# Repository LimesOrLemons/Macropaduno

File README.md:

# Macropaduno

An ESP32-S3 handheld controller with a custom PCB and 3D-printed enclosure for numerous programmable functions.

## Overview

Welcome to **Macropaduno**, a custom-designed handheld controller powered by an ESP32-S3. This is the second iteration of the design, significantly expanded to pack maximum functionality into a compact layout for advanced programming and testing.

## Features & Hardware Specs

* **Microcontroller:** ESP32-S3
* **Connectivity:** Bluetooth & Wi-Fi
* **Power Management:** Integrated battery management, internal power system, and a voltage booster (3.3V to 5V)
* **Audio:** Onboard speaker driven by an audio amplifier
* **Visuals:** OLED screen, camera module (OV2640), and addressable RGB LED
* **Input Controls:**
* 9x Mechanical key switches
* 2x Pressable joysticks
* 1x Pressable rotary encoder switch

* **Expansion:** Dedicated servo/header port for external peripherals and motors

## Project Journey & Lessons Learned

This design represents about a month of intensive work on the digital and schematic design side. Moving from a much smaller initial prototype, this version integrates all peripheral components onto a single custom PCB paired with a 3D-printed enclosure.

While the form factor turned out a bit bulkier than originally planned, it serves as an exceptional foundation for future iterations. Key engineering takeaways from this project include:

* Introduction to KiCad schematic and PCB layout & practices
* C++ firmware development for the ESP32-S3 and electronic components
* Planning for acoustic chambers, battery integration, and mechanical clearance in 3D CAD (modeled in Onshape, with future plans to explore SolidWorks for professional CAD workflows).
* Identifying areas for future optimization, such as transitioning to 4-layer boards and component stacking for tighter spatial efficiency.

## Version 1 Prototype
Here is what the v1 version of the macropad looked like:

## Version 2 Prototype
Here is what the v2 version of the macropad looked like:

## Acknowledgements & Credits

Special thanks to the open-source community and creators who shared CAD models and reference files used during the design process:

* [603040 600mAh LiPo Battery Cell on GrabCAD](https://grabcad.com/library/603040-600mah-lipo-battery-cell-1)
* [Cherry MX Switches on GrabCAD](https://grabcad.com/library/cherry-mx-switches-mx-1)
* [OV2640 Camera Model on GrabCAD](https://grabcad.com/library/ov2640-for-esp32-cam-1)
* [JST PH 2.0mm Connector Pack on GrabCAD](https://grabcad.com/library/jst-ph-2-0mm-connector-pack-through-hole-smt-ds1066-1)
* [Rotary Encoder on GrabCAD](https://grabcad.com/library/rotary-encoder-17)
* [0.91" OLED 128x32 Display on GrabCAD](https://grabcad.com/library/oled-0-91-128x32-1)
* [CherryMX GitHub Library by hineybush](https://github.com/hineybush/CherryMX/tree/master)

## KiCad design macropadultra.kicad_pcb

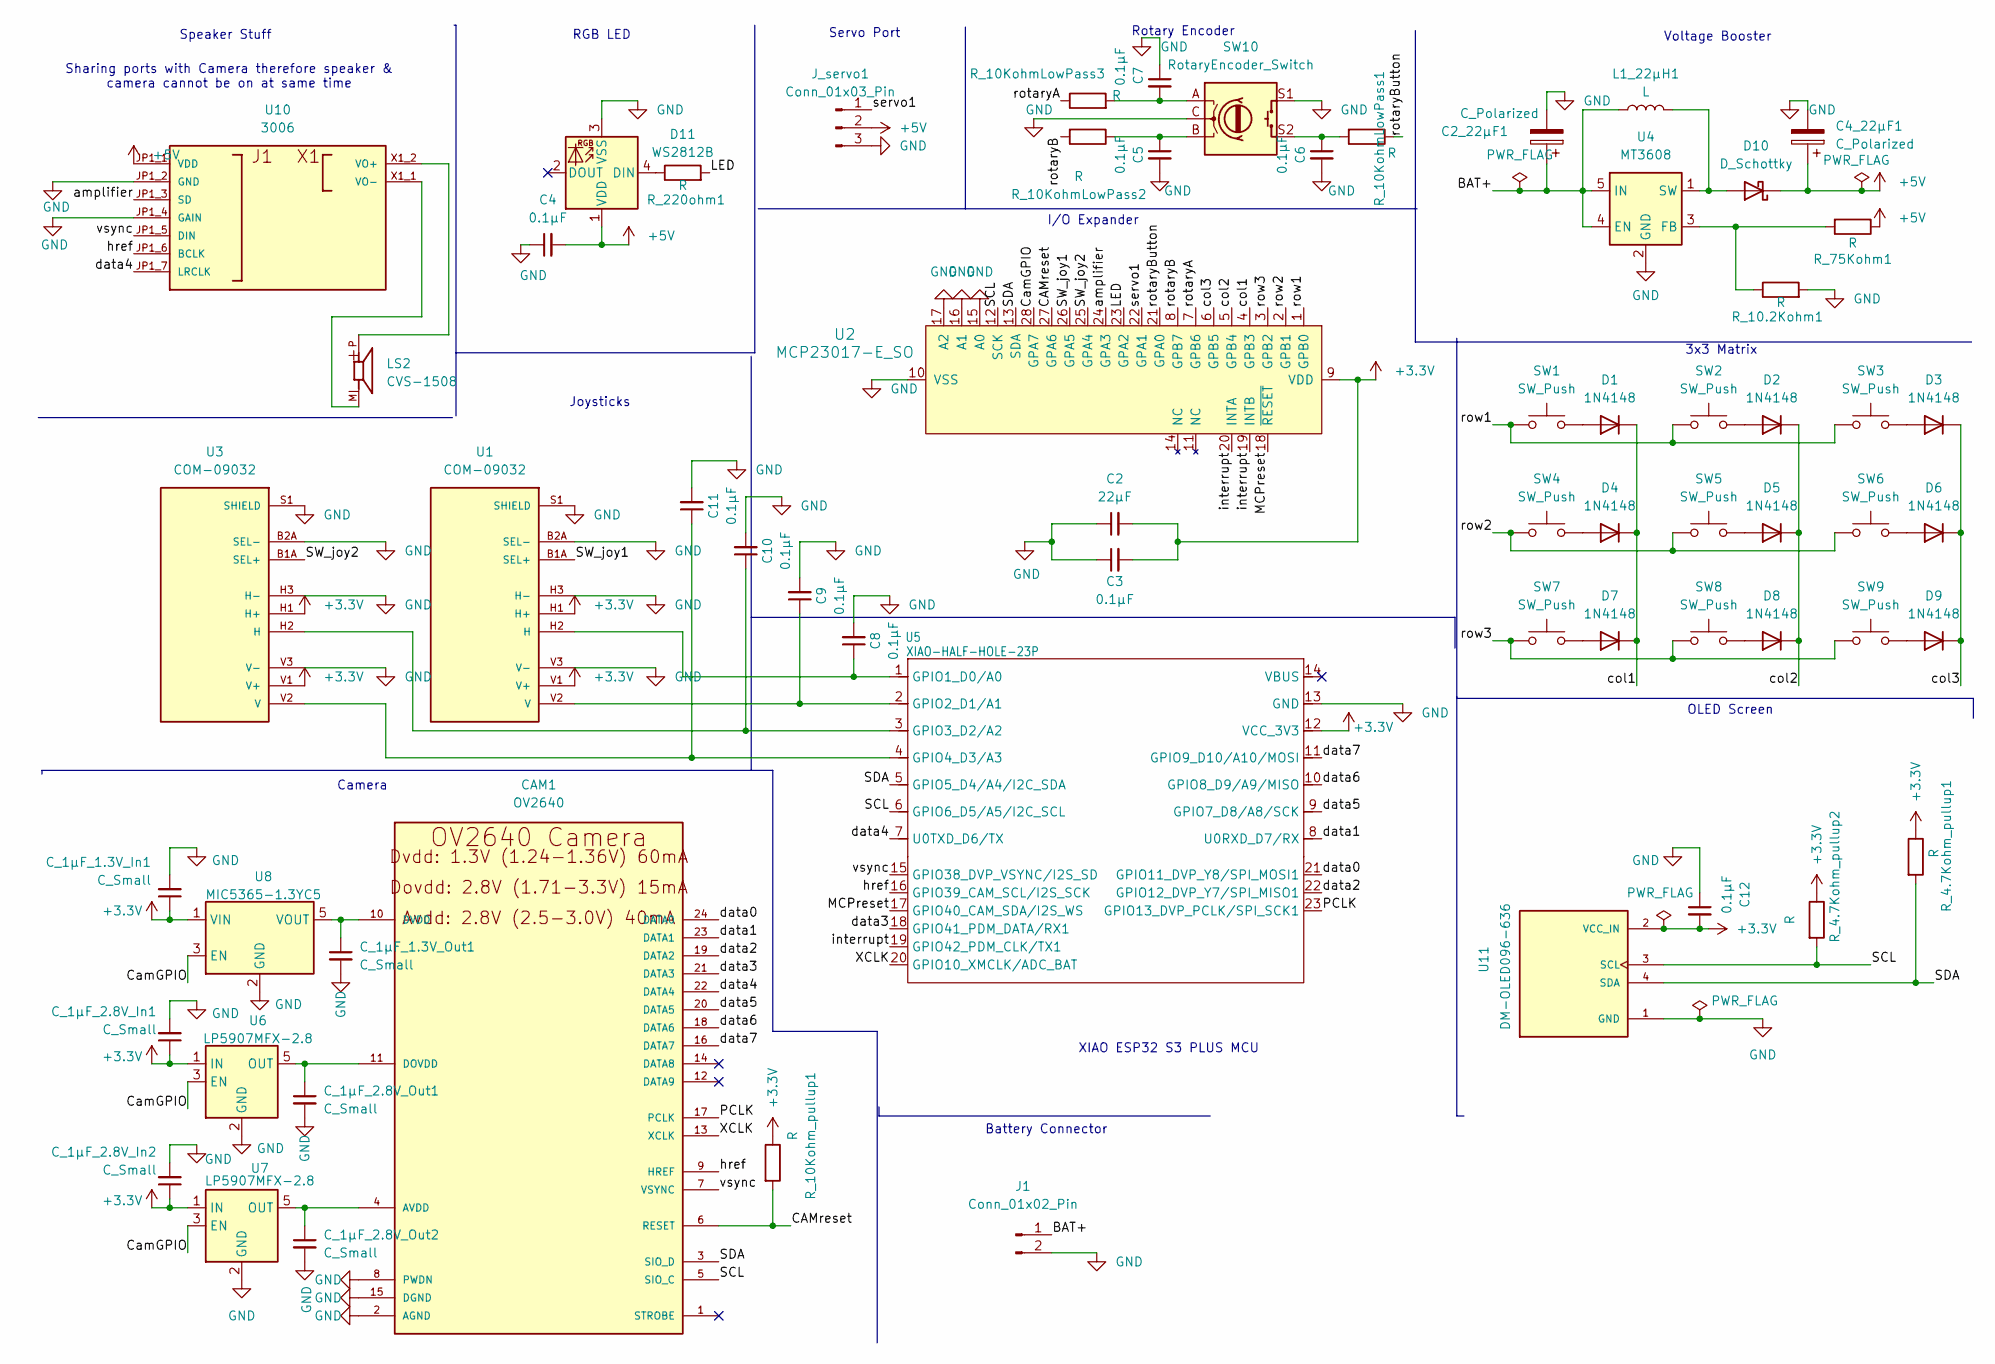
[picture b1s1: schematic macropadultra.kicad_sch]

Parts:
C2: 22µF; C_Disc_D5.0mm_W2.5mm_P5.00mm
C2_22µF1, C4_22µF1: C_Polarized; CP_Radial_D5.0mm_P2.00mm
C3, C4, C5, C6, C7, C8, C9, C10, C11, C12: 0.1µF; C_Disc_D5.0mm_W2.5mm_P5.00mm
CAM1: OV2640
C_1µF_1.3V_In1, C_1µF_1.3V_Out1, C_1µF_2.8V_In1, C_1µF_2.8V_In2, C_1µF_2.8V_Out1, C_1µF_2.8V_Out2: C_Small; C_Disc_D5.0mm_W2.5mm_P5.00mm
D1, D2, D3, D4, D5, D6, D7, D8, D9: 1N4148; D_DO-35_SOD27_P7.62mm_Horizontal
D10: D_Schottky; D_DO-41_SOD81_P10.16mm_Horizontal
D11: WS2812B; LED_WS2812B_PLCC4_5.0x5.0mm_P3.2mm
J1: Conn_01x02_Pin; JST_PH_S2B-PH-SM4-TB_1x02-1MP_P2.00mm_Horizontal
J_servo1: Conn_01x03_Pin; PinHeader_1x03_P2.54mm_Horizontal
L1_22µH1: L; L_Radial_D10.0mm_P5.00mm_Fastron_07M
LS2: CVS-1508; SPKR_CVS-1508
R_4.7Kohm_pullup1, R_4.7Kohm_pullup2, R_10.2Kohm1, R_10KohmLowPass1, R_10KohmLowPass2, R_10KohmLowPass3, R_10Kohm_pullup1, R_75Kohm1, R_220ohm1: R; R_Axial_DIN0207_L6.3mm_D2.5mm_P10.16mm_Horizontal
SW1, SW2, SW3, SW4, SW5, SW6, SW7, SW8, SW9: SW_Push; SW_Cherry_MX_1.00u_PCB
SW10: RotaryEncoder_Switch; RotaryEncoder_Alps_EC11E-Switch_Vertical_H20mm
U1, U3: COM-09032; XDCR_COM-09032; PARTREV N/A
U2: MCP23017-E_SO; SOIC-28_W7.5mm; MPN MCP23017-E/SO; Digi-Key_PN MCP23017-E/SO-ND
U4: MT3608; SOT-23-6
U5: XIAO-HALF-HOLE-23P; XIAO-ESP32-S3-Plus-SMD
U6, U7: LP5907MFX-2.8; SOT-23-5
U8: MIC5365-1.3YC5; SOT-353_SC-70-5
U10: 3006; MODULE_3006; PARTREV A
U11: DM-OLED096-636; MODULE_DM-OLED096-636; PARTREV 2018-09-10

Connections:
+3.3V: C2.2, C3.2, C12.2, C_1µF_1.3V_In1.1, C_1µF_2.8V_In1.1, C_1µF_2.8V_In2.1, R_4.7Kohm_pullup1.1, R_4.7Kohm_pullup2.1, R_10Kohm_pullup1.1, U1.H1 (H+), U1.V1 (V+), U2.9 (VDD), U3.H1 (H+), U3.V1 (V+), U5.12 (VCC_3V3), U6.1 (IN), U7.1 (IN), U8.1 (VIN), U11.2 (VCC_IN)
+5V: C4.2, C4_22µF1.1, D10.1 (K), D11.1 (VDD), J_servo1.2, R_75Kohm1.1, U10.JP1_1 (VDD)
/BAT+: C2_22µF1.1, J1.1, L1_22µH1.1, U4.4 (EN), U4.5 (IN), U5.32
/CAMreset: CAM1.6 (RESET), R_10Kohm_pullup1.2, U2.27 (GPA6)
/CamGPIO: U2.28 (GPA7), U6.3 (EN), U7.3 (EN), U8.3 (EN)
/LED: R_220ohm1.2, U2.23 (GPA2)
/MCPreset: U2.18 (~RESET), U5.17 (GPIO40_CAM_SDA/I2S_WS)
/PCLK: CAM1.17 (PCLK), U5.23 (GPIO13_DVP_PCLK/SPI_SCK1)
/SCL: CAM1.5 (SIO_C), R_4.7Kohm_pullup2.2, U2.12 (SCK), U5.6 (GPIO6_D5/A5/I2C_SCL), U11.3 (SCL)
/SDA: CAM1.3 (SIO_D), R_4.7Kohm_pullup1.2, U2.13 (SDA), U5.5 (GPIO5_D4/A4/I2C_SDA), U11.4 (SDA)
/SW_joy1: U1.B1A (SEL+), U2.26 (GPA5)
/SW_joy2: U2.25 (GPA4), U3.B1A (SEL+)
/XCLK: CAM1.13 (XCLK), U5.20 (GPIO10_XMCLK/ADC_BAT)
/amplifier: U2.24 (GPA3), U10.JP1_3 (SD)
/col1: D1.1 (K), D4.1 (K), D7.1 (K), U2.4 (GPB3)
/col2: D2.1 (K), D5.1 (K), D8.1 (K), U2.5 (GPB4)
/col3: D3.1 (K), D6.1 (K), D9.1 (K), U2.6 (GPB5)
/data0: CAM1.24 (DATA0), U5.21 (GPIO11_DVP_Y8/SPI_MOSI1)
/data1: CAM1.23 (DATA1), U5.8 (U0RXD_D7/RX)
/data2: CAM1.19 (DATA2), U5.22 (GPIO12_DVP_Y7/SPI_MISO1)
/data3: CAM1.21 (DATA3), U5.18 (GPIO41_PDM_DATA/RX1)
/data4: CAM1.22 (DATA4), U5.7 (U0TXD_D6/TX), U10.JP1_7 (LRCLK)
/data5: CAM1.20 (DATA5), U5.9 (GPIO7_D8/A8/SCK)
/data6: CAM1.18 (DATA6), U5.10 (GPIO8_D9/A9/MISO)
/data7: CAM1.16 (DATA7), U5.11 (GPIO9_D10/A10/MOSI)
/href: CAM1.9 (HREF), U5.16 (GPIO39_CAM_SCL/I2S_SCK), U10.JP1_6 (BCLK)
/interrupt: U2.19 (INTB), U2.20 (INTA), U5.19 (GPIO42_PDM_CLK/TX1)
/rotaryA: R_10KohmLowPass3.1, U2.7 (GPB6)
/rotaryB: R_10KohmLowPass2.2, U2.8 (GPB7)
/rotaryButton: R_10KohmLowPass1.1, U2.21 (GPA0)
/row1: SW1.1, SW2.1, SW3.1, U2.1 (GPB0)
/row2: SW4.1, SW5.1, SW6.1, U2.2 (GPB1)
/row3: SW7.1, SW8.1, SW9.1, U2.3 (GPB2)
/servo1: J_servo1.1, U2.22 (GPA1)
/vsync: CAM1.7 (VSYNC), U5.15 (GPIO38_DVP_VSYNC/I2S_SD), U10.JP1_5 (DIN)
GND: C2.1, C2_22µF1.2, C3.1, C4.1, C4_22µF1.2, C5.2, C6.2, C7.1, C8.2, C9.2, C10.2, C11.2, C12.1, CAM1.2 (AGND), CAM1.8 (PWDN), CAM1.15 (DGND), CAM1.MT1 (DGND), CAM1.MT2 (DGND), C_1µF_1.3V_In1.2, C_1µF_1.3V_Out1.2, C_1µF_2.8V_In1.2, C_1µF_2.8V_In2.2, C_1µF_2.8V_Out1.2, C_1µF_2.8V_Out2.2, D11.3 (VSS), J1.2, J_servo1.3, R_10.2Kohm1.2, SW10.C, SW10.S1, U1.B2A (SEL-), U1.H3 (H-), U1.S1 (SHIELD), U1.S2 (SHIELD), U1.S3 (SHIELD), U1.S4 (SHIELD), U1.V3 (V-), U2.10 (VSS), U2.15 (A0), U2.16 (A1), U2.17 (A2), U3.B2A (SEL-), U3.H3 (H-), U3.S1 (SHIELD), U3.S2 (SHIELD), U3.S3 (SHIELD), U3.S4 (SHIELD), U3.V3 (V-), U4.2 (GND), U5.13 (GND), U5.33, U6.2 (GND), U7.2 (GND), U8.2 (GND), U10.JP1_2 (GND), U10.JP1_4 (GAIN), U11.1 (GND)
unnamed: C5.1, R_10KohmLowPass2.1, SW10.B
unnamed: C6.1, R_10KohmLowPass1.2, SW10.S2
unnamed: C7.2, R_10KohmLowPass3.2, SW10.A
unnamed: CAM1.4 (AVDD), C_1µF_2.8V_Out2.1, U7.5 (OUT)
unnamed: CAM1.11 (DOVDD), C_1µF_2.8V_Out1.1, U6.5 (OUT)
unnamed: CAM1.10 (DVDD), C_1µF_1.3V_Out1.1, U8.5 (VOUT)
unnamed: D1.2 (A), SW1.2
unnamed: D2.2 (A), SW2.2
unnamed: D3.2 (A), SW3.2
unnamed: D4.2 (A), SW4.2
unnamed: D5.2 (A), SW5.2
unnamed: D6.2 (A), SW6.2
unnamed: D7.2 (A), SW7.2
unnamed: D8.2 (A), SW8.2
unnamed: D9.2 (A), SW9.2
unnamed: D10.2 (A), L1_22µH1.2, U4.1 (SW)
unnamed: D11.4 (DIN), R_220ohm1.1
unnamed: C8.1, U1.H2 (H), U5.1 (GPIO1_D0/A0)
unnamed: C9.1, U1.V2 (V), U5.2 (GPIO2_D1/A1)
unnamed: C10.1, U3.H2 (H), U5.3 (GPIO3_D2/A2)
unnamed: C11.1, U3.V2 (V), U5.4 (GPIO4_D3/A3)
unnamed: R_10.2Kohm1.1, R_75Kohm1.2, U4.3 (FB)
unnamed: LS2.P, U10.X1_2 (VO+)
unnamed: LS2.M, U10.X1_1 (VO-)

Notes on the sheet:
Joysticks
Voltage Booster
Battery Connector
Rotary Encoder
Camera
3x3 Matrix
OLED Screen
Sharing ports with Camera therefore speaker & camera cannot be on at same time
I/O Expander
RGB LED
Speaker Stuff
XIAO ESP32 S3 PLUS MCU
Servo Port

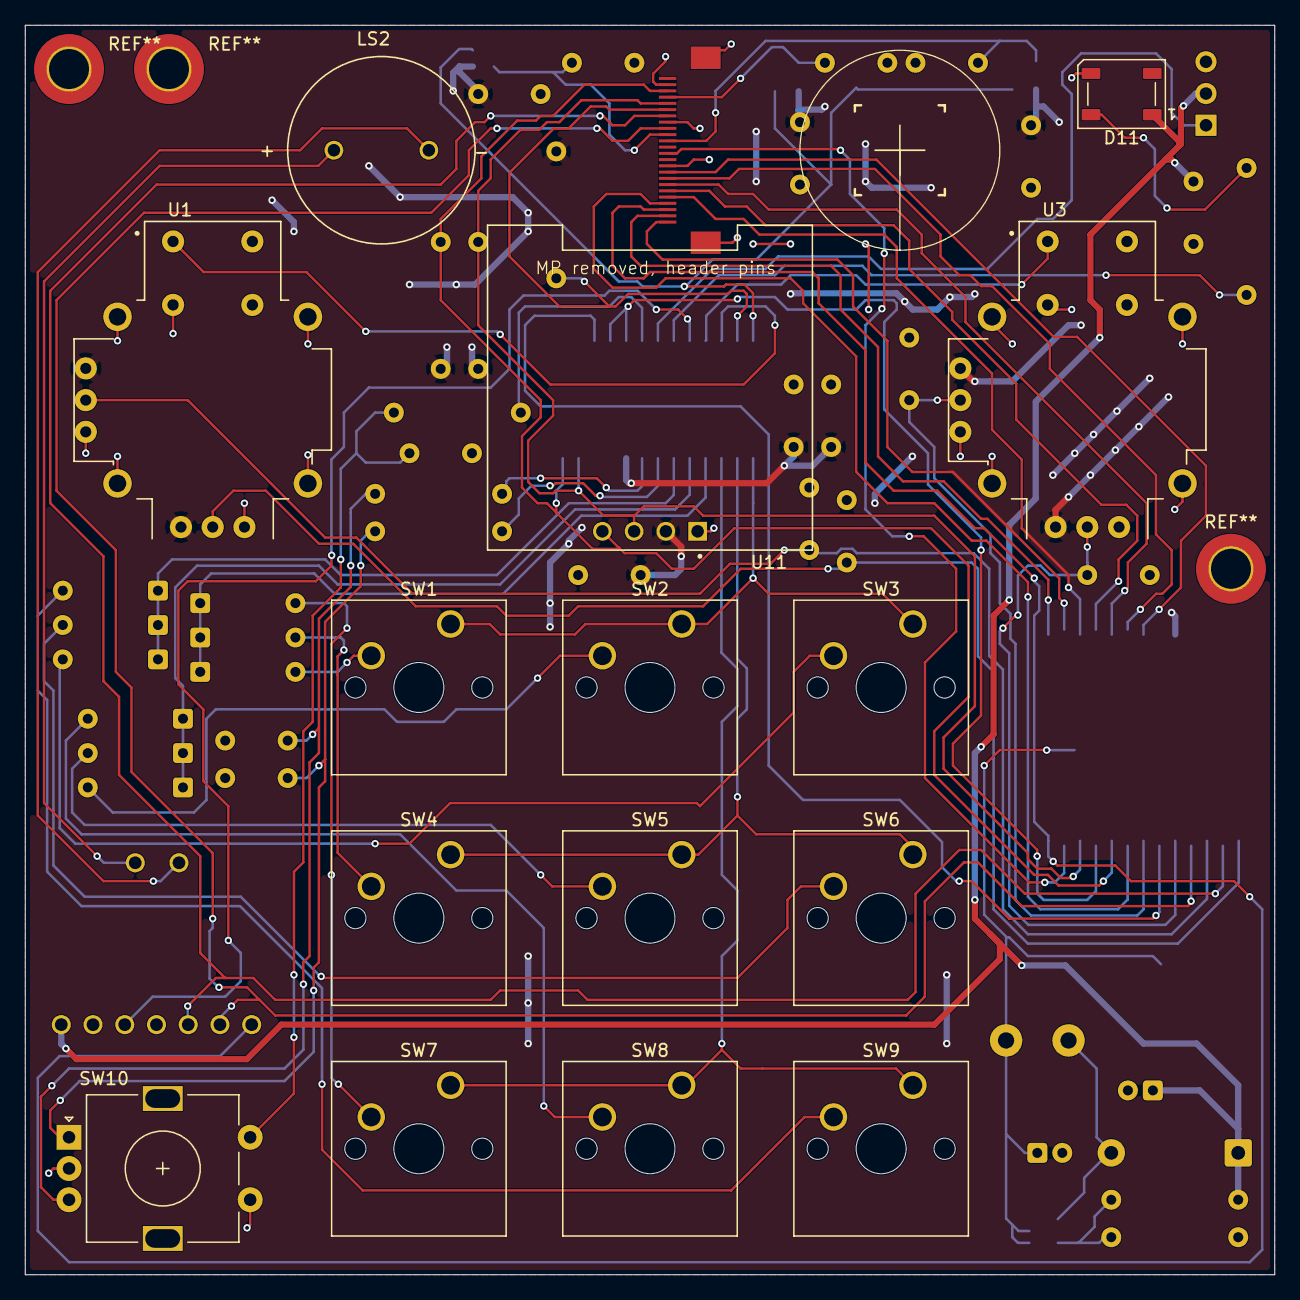
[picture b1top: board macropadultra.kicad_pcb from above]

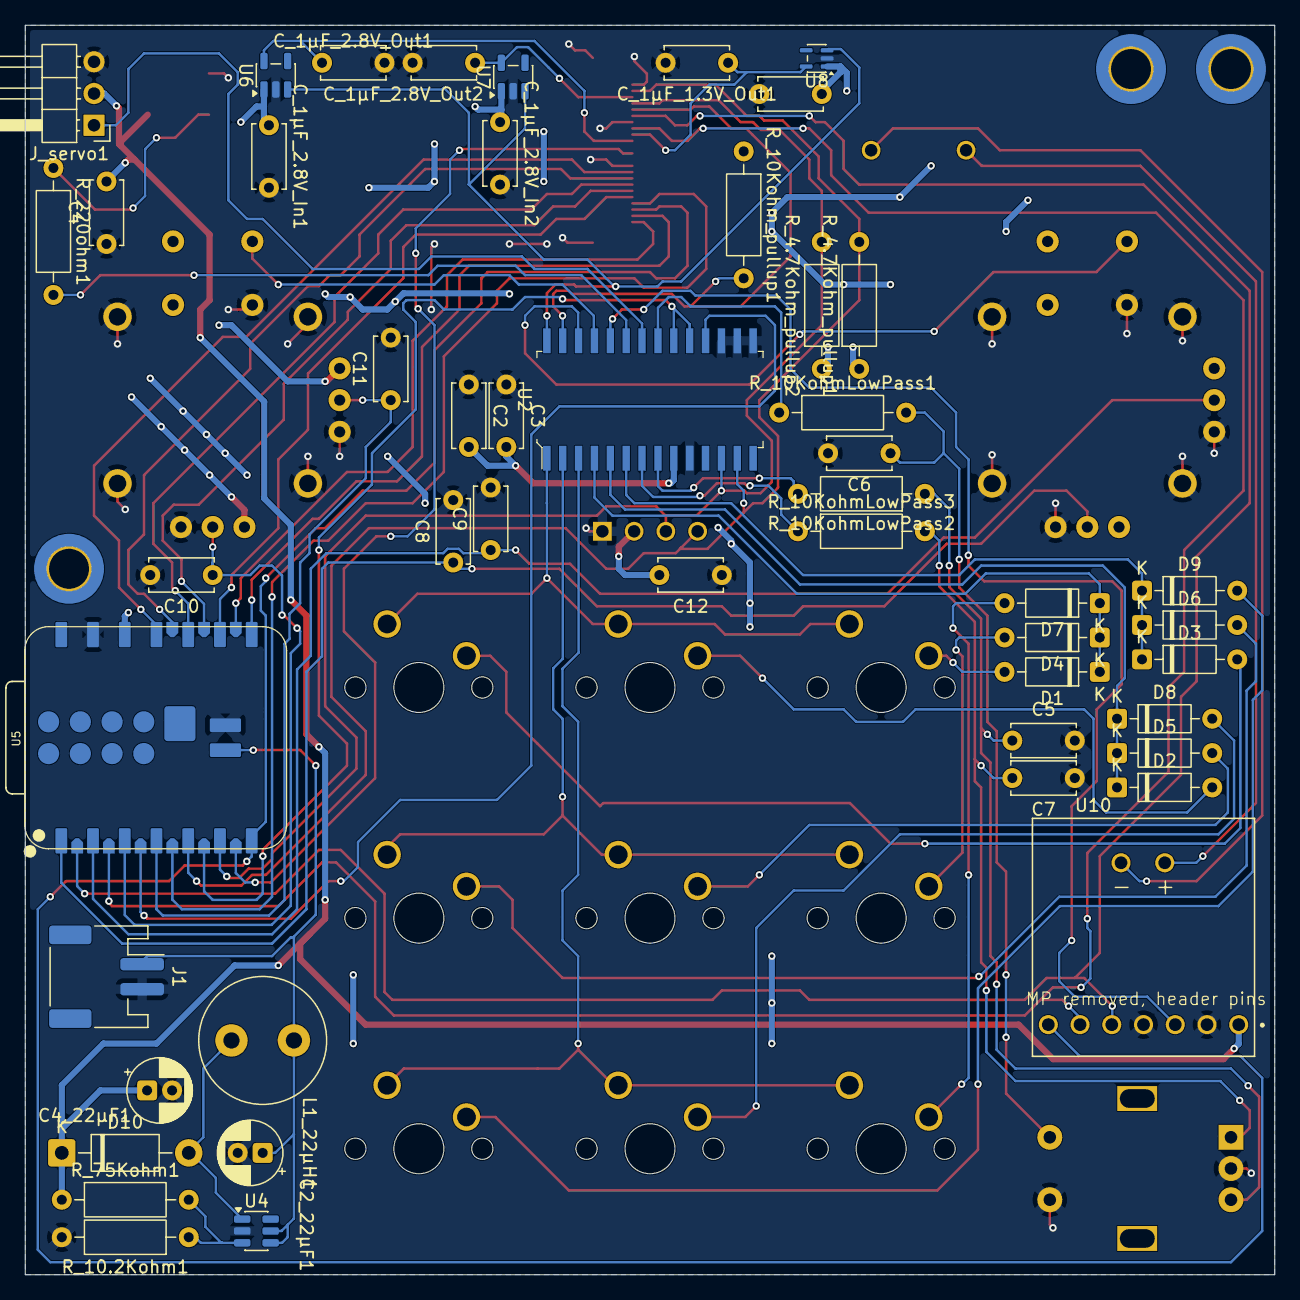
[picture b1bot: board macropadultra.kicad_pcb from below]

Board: 2 copper layers, 100.0 x 100.0 mm, 64 parts (48 on the bottom side), 60 nets.
